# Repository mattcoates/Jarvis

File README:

#Rocket Flight Computer

A generic flight computer for my level 1 and level 2 rockets.

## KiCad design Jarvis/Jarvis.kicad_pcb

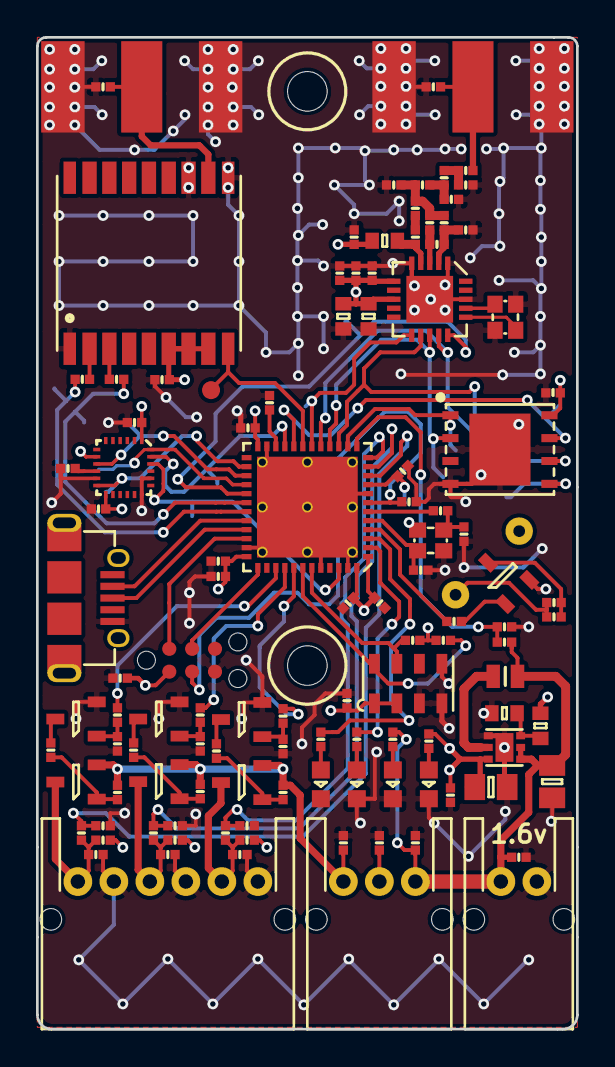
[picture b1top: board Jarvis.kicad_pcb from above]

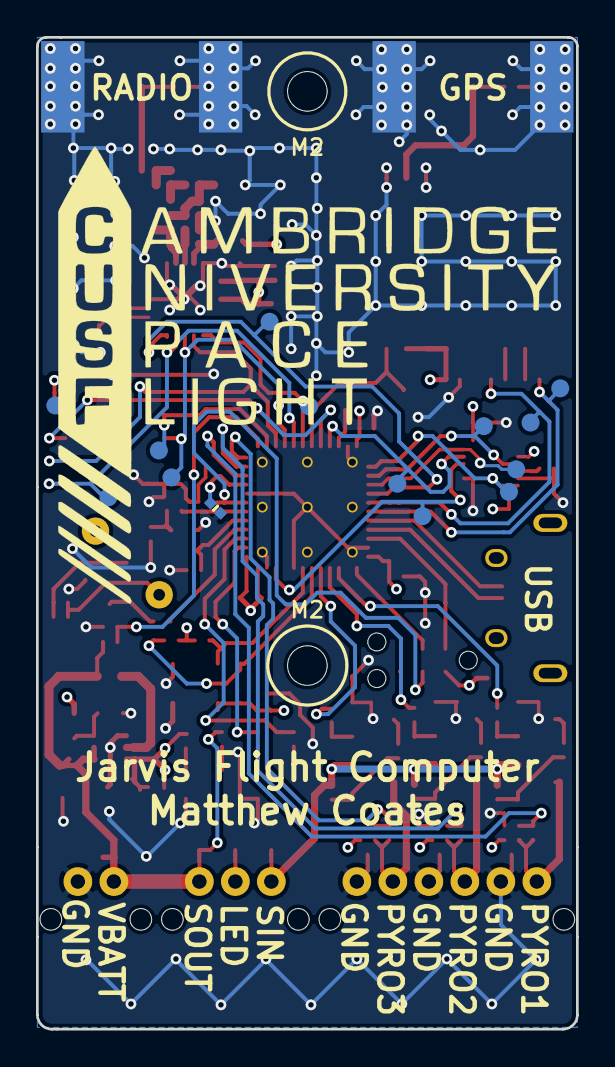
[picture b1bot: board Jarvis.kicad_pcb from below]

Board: 4 copper layers, 30.0 x 55.1 mm, 130 parts (16 on the bottom side), 76 nets.

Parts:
C1, C4, C5, C6, C8, C9, C10, C12, C13, C14, C15, C17, C20, C29, C30, C31, C34, C37: 100nF; 0402-L
C2, C3: 10uF; 0805
C7, C19: 4.7uF; 0402-L
C11: 10nF; 0402-L
C16: 1uF; 0402-L
C21, C22: 8pF; 0402-L
C23: 3pF; 0402-L
C24: 1.2pF; 0402-L
C25: 33pF; 0402-L
C26, C28: 5.1pF; 0402-L
C27: 10pF; 0402-L
C32: 2.2uF; 0603-L
C33: 1uF; 0603-L
C35: 100pF; 0402-L
C36: 220pF; 0402-L
D1, D2, D3, D4: LED; 0603-LED
D5, D6, D7, D8, D9, D10, D11, D12: ESD_DIODE; 0402-L
FB1, FB2: 1.25R; 0402-L
IC1: ADP1607; LFCSP-2x2
IC2: MAX-8Q; MAX-7Q
IC3: MPU-9250; QFN-24-MPU9250
IC4: STM32F411CxUx; QFN-48-EP-ST
IC5: Si4460; QFN-20-EP-SI
IC6: MS5611-01BA03; MS5611
IC7: S25FL127S
J1: PYRO; S06B-PASK-2
J2: PWR; S02B-PASK-2
J3: ARM; S03B-PASK-2
J4: MICROUSB; MICROUSB_MOLEX_47589-0001
L1: 2.2uH; VLF252012MT
L2: 18nH; 0402-L
L3: 22nH; 0402-L
L4, L5: 6.8nH; 0402-L
L6: 8.2nH; 0402-L
L7: 120nH; 0603-L
LS1: SOUNDER; AI-1027-TWT-3V-R
P1, P2: SMA; SMA-142-0701-801
P3: SWD_TC; TC2030-NL
Q1, Q2, Q3: PFET; SOT-23
Q4, Q5, Q6, Q7: NFET; SOT-23
R1, R2, R3, R12, R13, R14, R15, R16, R17, R18, R19, R20, R27, R28, R35, R36: 10k; 0402-L
R4, R5, R6, R8, R9, R10, R26, R29, R33, R34: 100R; 0402-L
R7: 330k; 0603-L
R11: 243k; 0603-L
R21, R22, R23, R24, R25: 1k; 0402-L
R32: 0R; 0402-L
TP15, TP19, TP23, TP27, TP28, TP30, TP31, TP32, TP33, TP36, TP37, TP39, TP43, TP44, TP49: TESTPAD
Y1: 26MHz; XTAL-20x16
Y2: 30MHz; XTAL-20x16

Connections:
3v3: C1.1, C3.1, C7.1, C8.1, C9.1, C10.1, C11.1, C12.1, C13.1, C14.1, C16.1, C17.1, C29.1, C30.1, C31.1, C32.1, C33.1, C34.1, C35.1, C36.1, C37.1, IC1.6, IC2.6, IC2.7, IC2.8, IC3.1, IC3.8, IC3.13, IC4.1, IC4.9, IC4.24, IC4.36, IC4.48, IC5.6, IC5.8, IC6.1, IC6.2, IC7.8, L7.2, LS1.1, P3.1, R7.2, R15.1, R16.1, R17.1, R21.1, R35.1, R36.1
/BATT_MON: IC4.13, R27.2, R28.1
/BEEPER: IC4.4, R34.1
/FLASH_RST: IC4.20, IC7.7, TP49.1
/GPS_RST: IC2.9, IC4.19, TP23.1
/I2C1_SCL: IC4.42, IC6.8, R35.2
/I2C1_SDA: IC4.43, IC6.7, R36.2
/MPU_IRQ: IC3.12, IC4.26, TP32.1
/PYRO1: D9.2, J1.1, Q1.3, R15.2, R18.2
/PYRO1_F: IC4.39, R8.1
/PYRO1_S: C4.1, IC4.10, R18.1
/PYRO2: D8.2, J1.3, Q2.3, R16.2, R19.2
/PYRO2_F: IC4.40, R9.1
/PYRO2_S: C5.1, IC4.11, R19.1
/PYRO3: D7.2, J1.5, Q3.3, R17.2, R20.2
/PYRO3_F: IC4.41, R10.1
/PYRO3_S: C6.1, IC4.12, R20.1
/PYRO_SO: D10.2, J3.1, Q1.2, Q2.2, Q3.2, R1.1, R2.1, R3.1
/Radio_nIRQ: IC4.18, IC5.11, TP43.1
/SPI1_MISO: IC4.16, IC5.13, IC7.2, TP37.1
/SPI1_MOSI: IC4.17, IC5.14, IC7.5, TP39.1
/SPI1_NSS1_FLASH: IC4.14, IC7.1, TP33.1
/SPI1_NSS2_RADIO: IC4.29, IC5.15, TP44.1
/SPI1_SCK: IC4.15, IC5.12, IC7.6, TP36.1
/SPI2_MISO: IC3.9, IC4.27, TP27.1
/SPI2_MOSI: IC3.24, IC4.28, TP30.1
/SPI2_NSS1_MPU: IC3.22, IC4.46, TP28.1
/SPI2_SCK: IC3.23, IC4.21, TP31.1
/STAT_HBT: IC4.2, R23.1
/STAT_WRN: IC4.3, R24.1
/SWCLK: IC4.37, P3.4
/SWDIO: IC4.34, P3.2
/USART1_RX: FB1.1, IC4.31, TP15.1
/USART1_TX: FB2.1, IC4.30, TP19.1
/USB_OTG_DM: IC4.32, J4.2
/USB_OTG_DP: IC4.33, J4.3
/~RST: C20.1, IC4.7, P3.3
GND: C1.2, C2.2, C3.2, C4.2, C5.2, C6.2, C7.2, C8.2, C9.2, C10.2, C11.2, C12.2, C13.2, C14.2, C15.2, C16.2, C17.2, C19.1, C20.2, C21.1, C22.1, C23.1, C26.2, C27.2, C28.2, C29.2, C30.2, C31.2, C32.2, C33.2, C34.2, C35.2, C36.2, C37.2, D1.1, D2.1, D3.1, D4.1, D5.1, D6.1, D7.1, D8.1, D9.1, D10.1, D11.1, D12.2, IC1.4, IC1.7, IC2.1, IC2.10, IC2.12, IC3.11, IC3.18, IC3.20, IC4.8, IC4.23, IC4.35, IC4.44, IC4.47, IC4.EP, IC5.1, IC5.5, IC5.18, IC5.EP, IC6.3, IC6.4, IC6.5, IC7.4, IC7.9, J1.2, J1.4, J1.6, J2.2, J4.5, P1.2, P1.3, P1.4, P1.5, P2.2, P2.3, P2.4, P2.5, P3.5, Q4.2, Q5.2, Q6.2, Q7.2, R11.2, R12.2, R13.2, R14.2, R25.2, R28.2, Y1.2, Y1.4, Y2.2, Y2.4
unnamed: C15.1, IC3.10
unnamed: C19.2, IC4.22
unnamed: C21.2, IC4.5, Y1.1
unnamed: C22.2, R26.1, Y1.3
unnamed: C23.2, IC5.2, L2.2, L3.1
unnamed: C24.1, IC5.3, L2.1
unnamed: C24.2, C26.1, L3.2, L4.1, L6.2
unnamed: C25.1, IC5.4, L7.1
unnamed: C25.2, L6.1
unnamed: C27.1, L4.2, L5.1
unnamed: C28.1, L5.2, R32.1
unnamed: D1.2, R21.2
unnamed: D2.2, R22.2
unnamed: D3.2, R23.2
unnamed: D4.2, R24.2
unnamed: D11.2, IC2.11, P1.1
unnamed: D12.1, P2.1, R32.2
unnamed: FB1.2, IC2.2
unnamed: FB2.2, IC2.3
unnamed: IC1.3, R7.1, R11.1
unnamed: IC1.5, L1.2
unnamed: IC4.6, R26.2
unnamed: IC5.16, Y2.1
unnamed: IC5.17, Y2.3
unnamed: J3.2, R25.1
unnamed: LS1.2, R29.1, R33.1
unnamed: Q1.1, R1.2, R4.2
unnamed: Q2.1, R2.2, R5.2
unnamed: Q3.1, R3.2, R6.2
unnamed: Q4.1, R8.2, R12.1
unnamed: Q4.3, R4.1
unnamed: Q5.1, R9.2, R13.1
unnamed: Q5.3, R5.1
unnamed: Q6.1, R10.2, R14.1
unnamed: Q6.3, R6.1
unnamed: Q7.1, R34.2
unnamed: Q7.3, R29.2, R33.2
VBATT: C2.1, D5.2, D6.2, IC1.1, IC1.2, J2.1, J3.3, L1.1, R22.1, R27.1

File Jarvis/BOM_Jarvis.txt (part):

Bill Of Materials
=================

Source file: Jarvis.xml
Date: 2016-04-19T19:52:06.596366

Parts Missing Footprints
------------------------
X1     434MHz ANT     
X5     ARM Switch     
X2     Red LED        
X4     AA Holder      
X3     AA Battery     
X8     Housing x1     
X9     Housing x4     
X10    Housing x1     
X13    F Crimps x17   
X6     Wire           
X14    Crimp Tool     
X12    M Crimps x6    
X7     Heat Shrink    
X11    Housing x3     
X16    RF Cover       

Parts Missing Order Codes
-------------------------
P3     SWD_TC          agg:TC2030-NL
X13    F Crimps x17    None
X6     Wire            None
X12    M Crimps x6     None
X7     Heat Shrink     None
TP19   TESTPAD         agg:TESTPAD
TP15   TESTPAD         agg:TESTPAD
TP6    TESTPAD         agg:TESTPAD
TP11   TESTPAD         agg:TESTPAD
TP4    TESTPAD         agg:TESTPAD
TP10   TESTPAD         agg:TESTPAD
TP12   TESTPAD         agg:TESTPAD
TP7    TESTPAD         agg:TESTPAD
TP1    TESTPAD         agg:TESTPAD
TP16   TESTPAD         agg:TESTPAD
TP14   TESTPAD         agg:TESTPAD
TP9    TESTPAD         agg:TESTPAD
TP3    TESTPAD         agg:TESTPAD
TP18   TESTPAD         agg:TESTPAD
TP13   TESTPAD         agg:TESTPAD
TP8    TESTPAD         agg:TESTPAD
TP2    TESTPAD         agg:TESTPAD
TP17   TESTPAD         agg:TESTPAD
TP26   TESTPAD         agg:TESTPAD
TP25   TESTPAD         agg:TESTPAD
TP24   TESTPAD         agg:TESTPAD
TP20   TESTPAD         agg:TESTPAD
TP21   TESTPAD         agg:TESTPAD
TP22   TESTPAD         agg:TESTPAD
TP38   TESTPAD         agg:TESTPAD
TP40   TESTPAD         agg:TESTPAD
TP33   TESTPAD         agg:TESTPAD
TP37   TESTPAD         agg:TESTPAD
TP39   TESTPAD         agg:TESTPAD
TP36   TESTPAD         agg:TESTPAD
TP44   TESTPAD         agg:TESTPAD
TP45   TESTPAD         agg:TESTPAD
TP41   TESTPAD         agg:TESTPAD
TP42   TESTPAD         agg:TESTPAD
TP47   TESTPAD         agg:TESTPAD
TP48   TESTPAD         agg:TESTPAD
TP43   TESTPAD         agg:TESTPAD
TP23   TESTPAD         agg:TESTPAD
TP32   TESTPAD         agg:TESTPAD
TP30   TESTPAD         agg:TESTPAD
TP31   TESTPAD         agg:TESTPAD
TP28   TESTPAD         agg:TESTPAD
TP27   TESTPAD         agg:TESTPAD
TP29   TESTPAD         agg:TESTPAD
TP35   TESTPAD         agg:TESTPAD
TP46   TESTPAD         agg:TESTPAD
TP34   TESTPAD         agg:TESTPAD
TP5    TESTPAD         agg:TESTPAD
TP49   TESTPAD         agg:TESTPAD

Inconsistent Order Codes
------------------------


Vendor Specific BOMs
--------------------
  RS
  ~~
883-7942,1,,1x--MPU-9250--QFN-24-MPU9250--IC3


  Digikey
  ~~~~~~~
1,AI-1027-TWT-3V-R,1x SOUNDER AI-1027-TWT-3V-R LS1


  Farnell
  ~~~~~~~
2524673,1,1x 10nF 0402-L
2346896,1,1x 2.2uF 0603-L
2455292,1,1x 2.2uH Neosid_Inductor_SM-NE
2310320,2,2x 8.2pF 0402-L
1760988,2,2x 18nH 0402-L
2497715,1,1x RF Frame BMI-S-201-F
2497714,1,1x RF Cover None
1226390,1,1x LED 0603-LED
1830730,1,1x Housing x1 None
2072516,5,5x 1k 0402-L
2072517,16,16x 10k 0402-L
1568023,1,1x MICROUSB MICROUSB_MOLEX_475
1830751,1,1x PYRO S06B-PASK-2
1515785 ,2,2x 1.25R 0402-L
2254940,1,1x ADP1607 LFCSP-2x2
2496792,1,1x 100pF 0402-L
2112849,1,1x 1uF 0603-L
1669639,3,3x 56nH 0402-L
1510761 ,4,4x NFET SOT-23
1894738,3,3x PFET SOT-23
1759381,1,1x 1uF 0402-L
2331061,1,1x 243k 0603-L
1226372,3,3x LED 0603-LED
2293260 ,1,1x AA Holder None
1657936,2,2x 10uF 0805
1863178,1,1x Red LED None
1830747,1,1x PWR S02B-PASK-2
1828860,18,18x 100nF 0402-L
1830726,1,1x Housing x4 None
1758939,2,2x 8pF 0402-L
1830728,1,1x Housing x1 None
1973025,1,1x 15pF 0402-L
1830748,1,1x ARM S03B-PASK-2
1608592,1,1x SMA SMA-142-0701-801
2362662,1,1x MS5611-01BA03 MS5611
1885342,1,1x 18pF 0402-L
2462635,1,1x Si4460 QFN-20-EP-SI
1469661,1,1x 0R 0402-L
1830756 ,1,1x Housing x3 None
2328003,1,1x S25FL127S WND008
2506973,1,1x 30MHz XTAL-20x16
2496800,1,1x 220pF 0402-L
1358015,10,10x 100R 0402-L
2456965,1,1x STM32F411CxUx QFN-48-EP-ST
1885321,1,1x 5.1pF 0402-L
2506952,1,1x 26MHz XTAL-20x16
2426952,2,2x 4.7uF 0402-L
2368169,8,8x ESD_DIODE 0402-L
2310308,1,1x 2.7pF 0402-L
2215631,1,1x 220nH 0603-L
1735379,1,1x ARM Switch None
2483918 ,1,1x 330k 0603-L


  eBay
  ~~~~
http://tinyurl.com/zxwhzow,1,1x X3 None
http://tinyurl.com/jokv8kj,1,1x X14 None


  HabSupplies
  ~~~~~~~~~~~
HAB-434STUB,1,1x X1 None
HAB-MAX-M8Q,1,1x IC2 MAX-7Q
HAB-SL1252R,1,1x P1 SMA-142-0701-801


Assembly BOM
------------
883-7942             1   MPU-9250        QFN-24-MPU9250  IC3
AI-1027-TWT-3V-R     1   SOUNDER         AI-1027-TWT-3V-R LS1
2524673              1   10nF            0402-L          C11
2346896              1   2.2uF           0603-L          C32
2455292              1   2.2uH           Neosid_Inductor_SM-NE29_SMD1008 L1
2310320              2   8.2pF           0402-L          C26 C28
1760988              2   18nH            0402-L          L4 L5
2497715              1   RF Frame        BMI-S-201-F     X15
2497714              1   RF Cover        None            X16
1226390              1   LED             0603-LED        D4
1830730              1   Housing x1      None            X10
2072516              5   1k              0402-L          R21 R22 R23 R24 R25
2072517              16  10k             0402-L          R1 R12 R13 R14 R15 R16 R17 R18 R19 R2 R20 R27 R28 R3 R35 R36
1568023              1   MICROUSB        MICROUSB_MOLEX_47589-0001 J4
1830751              1   PYRO            S06B-PASK-2     J1
1515785              2   1.25R           0402-L          FB1 FB2
2254940              1   ADP1607         LFCSP-2x2       IC1
2496792              1   100pF           0402-L          C35
2112849              1   1uF             0603-L          C33
1669639              3   56nH            0402-L          L2 L3 L6
1510761              4   NFET            SOT-23          Q4 Q5 Q6 Q7
1894738              3   PFET            SOT-23          Q1 Q2 Q3
1759381              1   1uF             0402-L          C16
2331061              1   243k            0603-L          R11
1226372              3   LED             0603-LED        D1 D2 D3
2293260              1   AA Holder       None            X4
1657936              2   10uF            0805            C2 C3
1863178              1   Red LED         None            X2
1830747              1   PWR             S02B-PASK-2     J2
1828860              18  100nF           0402-L          C1 C10 C12 C13 C14 C15 C17 C20 C29 C30 C31 C34 C37 C4 C5 C6 C8 C9
1830726              1   Housing x4      None            X9
1758939              2   8pF             0402-L          C21 C22
1830728              1   Housing x1      None            X8
1973025              1   15pF            0402-L          C27
1830748              1   ARM             S03B-PASK-2     J3
1608592              1   SMA             SMA-142-0701-801 P2
2362662              1   MS5611-01BA03   MS5611          IC6
1885342              1   18pF            0402-L          C25
2462635              1   Si4460          QFN-20-EP-SI    IC5
1469661              1   0R              0402-L          R32
1830756              1   Housing x3      None            X11
2328003              1   S25FL127S       WND008          IC7
2506973              1   30MHz           XTAL-20x16      Y2
2496800              1   220pF           0402-L          C36
1358015              10  100R            0402-L          R10 R26 R29 R33 R34 R4 R5 R6 R8 R9
2456965              1   STM32F411CxUx   QFN-48-EP-ST    IC4
1885321              1   5.1pF           0402-L          C23
2506952              1   26MHz           XTAL-20x16      Y1
2426952              2   4.7uF           0402-L          C19 C7
2368169              8   ESD_DIODE       0402-L          D10 D11 D12 D5 D6 D7 D8 D9
2310308              1   2.7pF           0402-L          C24
2215631              1   220nH           0603-L          L7
1735379              1   ARM Switch      None            X5
2483918              1   330k            0603-L          R7
http://tinyurl.com/zxwhzow 1   AA Battery      None            X3
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
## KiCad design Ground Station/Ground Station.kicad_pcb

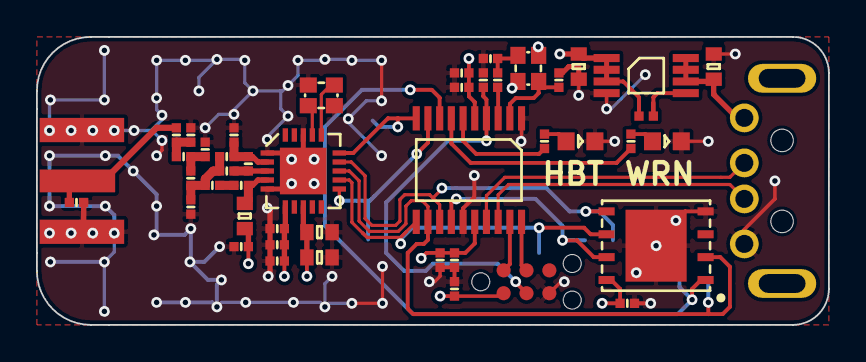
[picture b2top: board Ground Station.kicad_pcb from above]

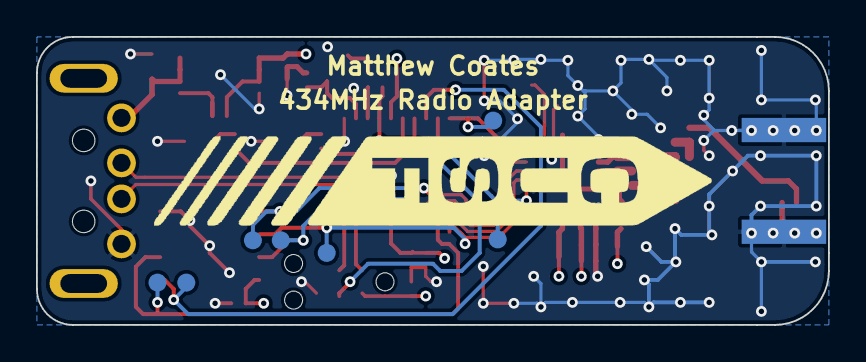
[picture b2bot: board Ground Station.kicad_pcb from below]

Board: 4 copper layers, 44.0 x 16.0 mm, 54 parts (7 on the bottom side), 33 nets.

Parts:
C1: 3pF; 0402-L
C2: 1nF; 0402-L
C3: 1.2pF; 0402-L
C4: 33pF; 0402-L
C5, C6, C11: 2.2uF; 0603-L
C7, C9: 5.1pF; 0402-L
C8: 10pF; 0402-L
C10, C13, C16, C19, C20, C23, C24: 100nF; 0402-L
C12: 1uF; 0603-L
C14: 100pF; 0402-L
C15: 220pF; 0402-L
C17, C18: 8pF; 0402-L
C21: 1uF; 0402-L
C22: 4.7uF; 0402-L
D1: ESD_DIODE; 0402-L
D2, D3: LED; 0603-LED
IC1: ADP3335; MSOP-8
IC2: STM32F042F6P6; TSSOP20
IC3: Si4460; QFN-20-EP-SI
IC4: S25FL127S
J1: USB-PLUG; MOLEX 48037-0001
L1: 18nH; 0402-L
L2: 22nH; 0402-L
L3, L4: 6.8nH; 0402-L
L5: 8.2nH; 0402-L
L6: 120nH; 0603-L
P1: SMA; SMA-J-P-H-ST-EM1
P2: SWD_TC; TC2030-NL
R1: 0R; 0402-L
R2: 100R; 0402-L
R3, R4: 1k; 0402-L
TP2, TP3, TP4, TP5, TP6, TP7, TP9: TESTPAD
X1: RF Frame; BMI-S-201-F
Y1: 30MHz; XTAL-20x16
Y2: 26MHz; XTAL-20x16

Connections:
3v3: C2.1, C6.1, C10.1, C11.1, C12.1, C13.1, C14.1, C15.1, C16.1, C19.1, C20.1, C21.1, C22.1, C23.1, IC1.1, IC1.2, IC1.3, IC2.5, IC2.16, IC3.6, IC3.8, IC4.8, L6.2, P2.1
5v: C5.1, IC1.6, IC1.7, IC1.8, J1.1
/FLASH_RST: IC2.14, IC4.7, TP9.1
/Radio_nIRQ: IC2.9, IC3.11, TP4.1
/SPI1_MISO: IC2.12, IC3.13, IC4.2, TP3.1
/SPI1_MOSI: IC2.13, IC3.14, IC4.5, TP6.1
/SPI1_NSS_FLASH: IC2.8, IC4.1, TP7.1
/SPI1_NSS_RADIO: IC2.10, IC3.15, TP5.1
/SPI1_SCK: IC2.11, IC3.12, IC4.6, TP2.1
/STAT_HBT: IC2.6, R3.1
/STAT_WRN: IC2.7, R4.1
/SWCLK: IC2.20, P2.4
/SWDIO: IC2.19, P2.2
/USB_DM: IC2.17, J1.2
/USB_DP: IC2.18, J1.3
/~RST: C24.1, IC2.4, P2.3
GND: C1.1, C5.2, C6.2, C7.2, C8.2, C9.2, C10.2, C11.2, C12.2, C13.2, C14.2, C15.2, C16.2, C17.1, C18.1, C19.2, C20.2, C21.2, C22.2, C23.2, C24.2, D1.2, D2.1, D3.1, IC1.4, IC2.1, IC2.15, IC3.1, IC3.5, IC3.18, IC3.EP, IC4.4, IC4.9, J1.4, P1.2, P1.3, P1.4, P1.5, P2.5, Y1.2, Y1.4, Y2.2, Y2.4
unnamed: C1.2, IC3.2, L1.2, L2.1
unnamed: C2.2, IC1.5
unnamed: C3.1, IC3.3, L1.1
unnamed: C3.2, C7.1, L2.2, L3.1, L5.2
unnamed: C4.1, IC3.4, L6.1
unnamed: C4.2, L5.1
unnamed: C8.1, L3.2, L4.1
unnamed: C9.1, L4.2, R1.1
unnamed: C17.2, IC2.2, Y2.1
unnamed: C18.2, R2.1, Y2.3
unnamed: D1.1, P1.1, R1.2
unnamed: D2.2, R3.2
unnamed: D3.2, R4.2
unnamed: IC2.3, R2.2
unnamed: IC3.16, Y1.1
unnamed: IC3.17, Y1.3

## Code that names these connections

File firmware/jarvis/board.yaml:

name: Jarvis Flight Computer
lsefreq: 0
hsefreq: 26000000
voltage: 3.0
mcutype: STM32F411xE
default: input, pushpull, starthigh, pullup, highspeed
pins:
    SWDIO:      pa13, af0
    SWCLK:      pa14, pulldown, af0
    
    STAT_HBT:   pc13, output, pushpull, startlow
    STAT_WRN:   pc14, output, pushpull, startlow
    
    BEEP:       pc15, output, pushpull, startlow, pulldown
    
    BAT_MON:    pa3, analog, floating
    
    PYROS_1:    pa0, output, pushpull, startlow
    PYROS_2:    pa1, output, pushpull, startlow
    PYROS_3:    pa2, output, pushpull, startlow
    
    PYROF_1:    pb3, output, pushpull, startlow
    PYROF_2:    pb4, output, pushpull, startlow
    PYROF_3:    pb5, output, pushpull, startlow
    
    FLASH_CS:   pa4, output, pushpull
    RADIO_CS:   pa8, output, pushpull
    
    SPI1_MOSI:  pa7, af5
    SPI1_MISO:  pa6, af5
    SPI1_SCK:   pa5, af5
    
    USART1_TX:  pa9, af7
    USART1_RX:  pa10, af7
    
    USB_DM:     pa11, af10
    USB_DP:     pa12, af10
    
    RADIO_IRQ:  pb0, input
    GPS_RST:    pb1, output, pushpull, pullup
    FLASH_RST:  pb2, output, pushpull, pullup
    
    I2C1_SDA:   pb7, af4, opendrain
    I2C1_SCL:   pb6, af4, opendrain
    
    MPU_CS:     pb9, output, pushpull
    MPU_IRQ:    pb13, input
    
    SPI2_MOSI:  pb15, af5
    SPI2_MISO:  pb14, af5
    SPI2_SCK:   pb10, af5
    

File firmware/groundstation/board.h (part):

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/*
 *  GPIOA setup:
 *
 * PA0  - STAT_HBT                     (output, pushpull).
 * PA1  - STAT_WRN                     (output, pushpull).
 * PA2  - SPI1_NSS_FLASH               (output, pushpull).
 * PA3  - RADIO_NIRQ                   (input).
 * PA4  - SPI1_NSS_RADIO               (output, pushpull).
 * PA5  - SPI1_SCK                     (af0).
 * PA6  - SPI1_MISO                    (af0).
 * PA7  - SPI1_MOSI                    (af0).
 * PA8  - PIN8                         (unused).
 * PA9  - PIN9                         (unused).
 * PA10 - PIN10                        (unused).
 * PA11 - USB_DM                       (input).
 * PA12 - USB_DP                       (input).
 * PA13 - SWDIO                        (af0).
 * PA14 - SWCLK                        (pulldown, af0).
 * PA15 - PIN15                        (unused).
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 *  GPIOB setup:
 *
 * PB0  - PIN0                         (unused).
 * PB1  - FLASH_RST                    (output, pushpull).
 * PB2  - PIN2                         (unused).
 * PB3  - PIN3                         (unused).
 * PB4  - PIN4                         (unused).
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
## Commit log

2016-03-17 Init
2016-03-21 Completed Boost Converter
2016-03-24 Added External Connectors & STM32F411CxUx with peripherals configured
2016-03-25 Added Radio & Barometer
2016-03-25 Added gitignore
2016-03-25 Tidying up
2016-03-28 Progressed Schematic
2016-03-29 BOM near completion
2016-03-30 Started PCB Layout
2016-03-31 Schematic Complete
2016-03-31 Added Testpoints
2016-04-01 Added mounts & placed ecternal connectors
2016-04-04 Routed PSU
2016-04-06 Replaced SD Card with 16MB Flash and started placment
2016-04-08 Routing progress
2016-04-09 Continued Layout
2016-04-13 Continued PCB
2016-04-18 Ready to Check Footprints
2016-04-19 Finished PCB
2016-04-19 Started Ground Station Footprints
2016-04-21 Finished Ground Station Schemnatic
2016-04-21 Generated pdf
2016-04-23 Finished ground station
2016-04-23 Readme update
2016-05-07 Checked all Footprints
2016-05-08 All checked and panel completed
2016-05-08 Modified tolerence
2016-05-15 Generated gerbers
2016-06-21 Modified radio circuit to 868MHz and generated stickerBOM
2016-06-25 Corrected Radio Passives in Ground Station
2016-06-25 Tidy up before final assembly
2016-08-06 Starter firmware
2016-08-09 Started firmware
2016-08-10 LED now blinks
2016-09-03 Added board.yaml
2016-10-09 Jarvis firmware progress
2016-10-09 Clean up
2016-10-09 Started Jarvis Frimware
2016-10-09 Started EEPROM header
2016-12-05 Updated board.h
2016-12-06 DMA and CLK config
2016-12-06 EXT setup
2017-10-09 started barometer driver
2017-10-10 i2c driver trouble
2017-10-10 pressure sensor works
2017-10-11 added 1607
2017-10-12 added ADP1607 footprint to local library

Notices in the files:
firmware/groundstation/board.h:
ChibiOS - Copyright (C) 2006..2016 Giovanni Di Sirio
Licensed under the Apache License, Version 2.0 (the "License");
